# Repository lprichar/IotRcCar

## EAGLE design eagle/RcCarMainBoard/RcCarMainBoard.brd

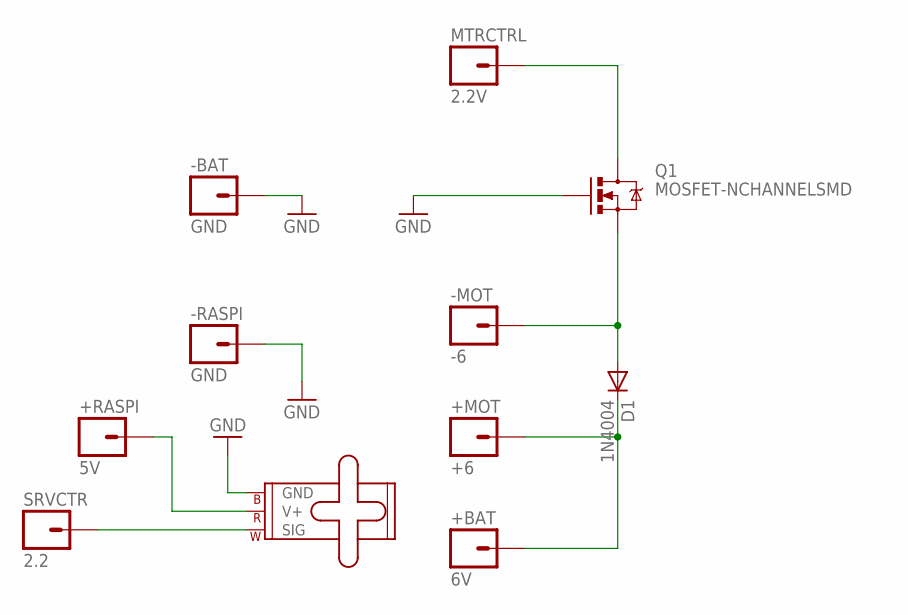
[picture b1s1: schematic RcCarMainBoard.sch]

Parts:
+BAT: 6V; 1X01
+MOT: +6; 1X01
+RASPI: 5V; 1X01
-BAT: GND; 1X01
-MOT: -6; 1X01
-RASPI: GND; 1X01
D1: 1N4004; DO41-10
M1: SMALL_SERVO; 1X03
MTRCTRL: 2.2V; 1X01
Q1: MOSFET-NCHANNELSMD; SOT23-3
SRVCTR: 2.2; 1X01

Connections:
GND: -BAT.1, -RASPI.1, M1.3 (GND), Q1.1 (G)
unnamed: +BAT.1, +MOT.1, D1.C
unnamed: -MOT.1, D1.A, Q1.2 (S)
unnamed: M1.1 (SIG), SRVCTR.1
unnamed: MTRCTRL.1, Q1.3 (D)
unnamed: +RASPI.1, M1.2 (V+)

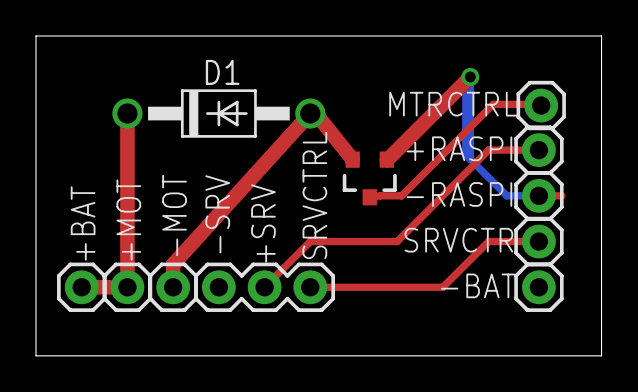
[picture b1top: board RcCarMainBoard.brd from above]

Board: 2 copper layers, 31.4 x 17.8 mm, 11 parts (0 on the bottom side), 6 nets.

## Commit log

2016-03-27 pwm pin driving motor
2016-03-27 Hello world webserver
2016-03-27 Use embedded resource rather than raw stream
2016-04-04 Server to client communication
2016-04-04 Successfully controlling a servo
2016-04-08 deduplicate pins
2016-04-09 A blank node express site
2016-04-10 Moved car control logic into web server background task
2016-04-10 fixed bug with sending percent incorrectly as 0-100 rather than 0-1
2016-04-10 Handle web server shutdown
2016-04-11 Moved all source code into /src and added a /cad folder for all the 3d models
2016-04-23 Fade new project just for blink
2016-04-23 RcCarMainBoard
2016-04-29 Fixing up the chassis to fit a battery pack
2016-04-29 Signalr sample code and misc cleanup
2016-04-29 Removed temporary projects
2016-04-29 Renamed IotHelloWorld to IotGuiTest
2016-04-30 Switched the servo controller over to PWM
2016-04-30 Control the car with an xbox controller
2016-04-30 send xbox signals to the http server
2017-11-07 Retargeted to creator's update and added the lightning providers via Nuget

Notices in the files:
parts and their libraries:
SparkFun-Connectors: Licensing: Creative Commons ShareAlike 4.0 International - https://creativecommons.org/licenses/by-sa/4.0
